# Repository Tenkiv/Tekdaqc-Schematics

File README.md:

# TekdaqcSchematics

pcb file for RevE and RevF are incomplete
- all digital grounds are currently unconnected
#TODO ground plane

RevE contains the files for the current Tekdaqc version

RevF is a modified version of the current Tekdaqc
- GIP15 is moved from PC14 to PH5
- GPI4 is moved from PH0 to PH3
- Digital Output connection has been modified to include a pull down resistor

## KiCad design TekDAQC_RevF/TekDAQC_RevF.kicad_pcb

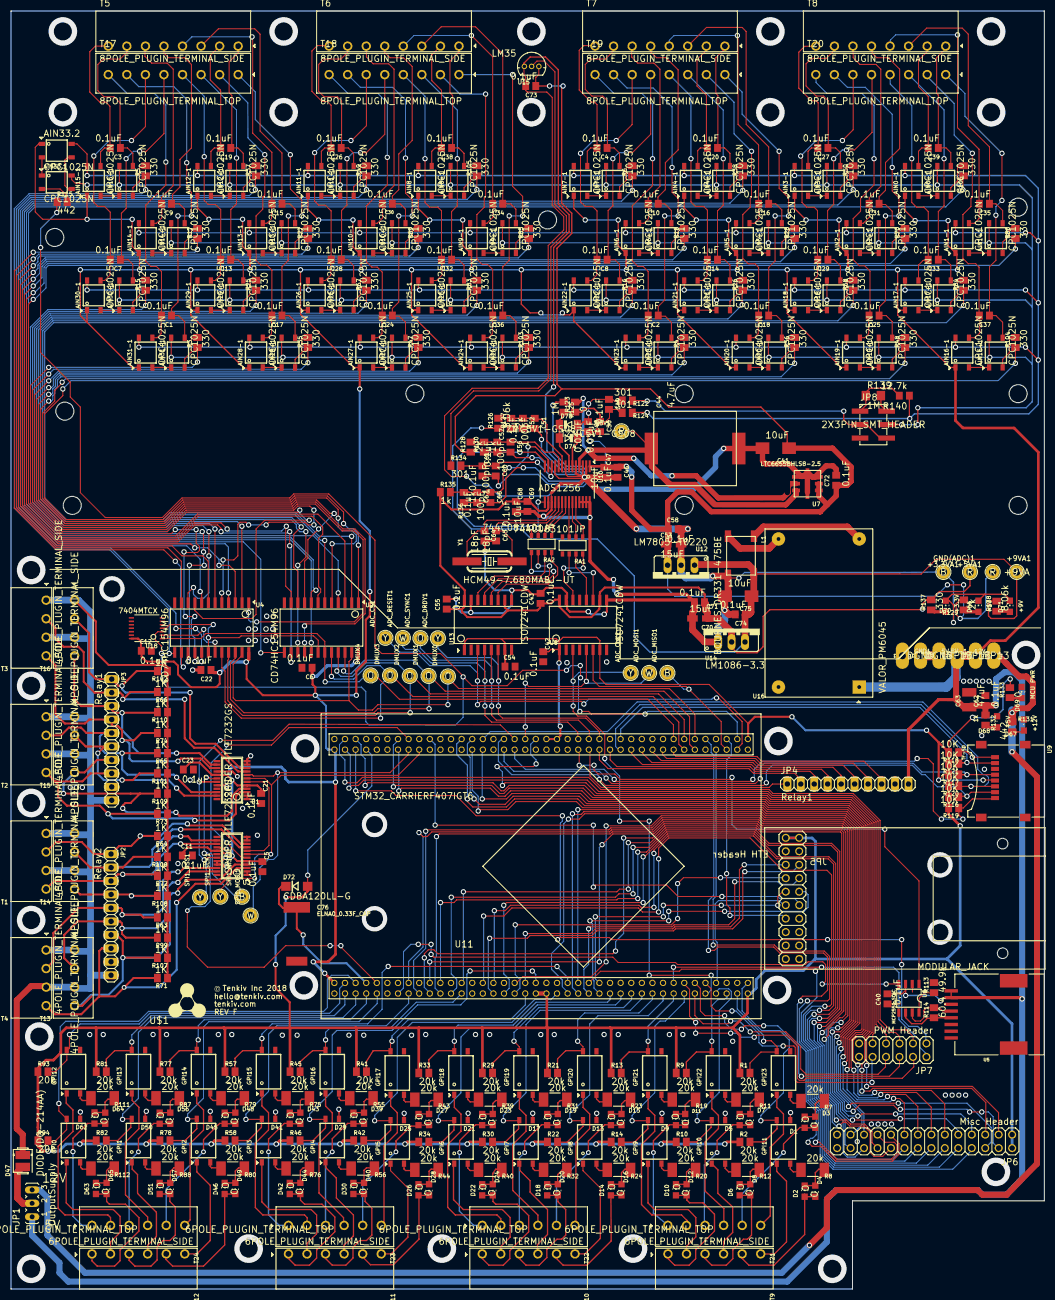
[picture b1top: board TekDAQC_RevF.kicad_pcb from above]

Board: 2 copper layers, 194.9 x 241.1 mm, 441 parts (0 on the bottom side), 430 nets.

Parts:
2.5V1: R; OTHER_KEYSTONE_5000
5V, 5V-1, 12V: LSP13
+3.3VA1, +5VA1: R; OTHER_KEYSTONE_5000
+9VA1: +9VA; OTHER_KEYSTONE_5000
@HOLE0, @HOLE1, @HOLE2, @HOLE3, @HOLE4, @HOLE6, @HOLE7, @HOLE8, @HOLE9, @HOLE10: (no value)
@HOLE5: HOLE_CIRCLE
@HOLE11, @HOLE12, @HOLE13, @HOLE14: HOLE_OVAL
ADC_CLK1: Y; OTHER_KEYSTONE_5000
ADC_CS1: Y; OTHER_KEYSTONE_5000
ADC_DRDY1: Y; OTHER_KEYSTONE_5000
ADC_MISO1: B; OTHER_KEYSTONE_5000
ADC_MOSI1: W; OTHER_KEYSTONE_5000
ADC_RESET1: W; OTHER_KEYSTONE_5000
ADC_SYNC1: O; OTHER_KEYSTONE_5000
AIN0+1, AIN0-1, AIN1+1, AIN1-1, AIN2+1, AIN2-1, AIN3+1, AIN3-1, AIN4+1, AIN4-1, AIN5+1, AIN5-1, AIN6+1, AIN6-1, AIN7+1, AIN7-1, AIN8+1, AIN8-1, AIN9+1, AIN9-1, AIN10+1, AIN10-1, AIN11+1, AIN11-1, AIN12+1, AIN12-1, AIN13+1, AIN13-1, AIN14+1, AIN14-1, AIN15+1, AIN15-1, AIN16+1, AIN16-1, AIN17+1, AIN17-1, AIN18+1, AIN18-1, AIN19+1, AIN19-1, AIN20+1, AIN20-1, AIN21+1, AIN21-1, AIN22+1, AIN22-1, AIN23+1, AIN23-1, AIN24+1, AIN24-1, AIN25+1, AIN25-1, AIN26+1, AIN26-1, AIN27+1, AIN27-1, AIN28+1, AIN28-1, AIN29+1, AIN29-1, AIN30+1, AIN30-1, AIN31+1, AIN31-1, AIN33.1, AIN33.2: CPC1025N; CPC1025N_SOP4
C1, C2, C3, C4, C5, C6, C7, C8, C9, C10, C11, C12, C13, C14, C15, C16, C17, C18, C19, C20, C21, C22, C23, C24, C25, C26, C27, C28, C29, C30, C31, C32, C33, C34, C35, C36, C37, C38, C39, C40, C42, C43, C46, C49, C52, C54, C55, C57, C58, C61, C62, C67, C68, C71, C72, C73, C74: 0.1uF; CAPACITOR_C0805
C41, C75: 10uF; CAPACITOR_CT6032
C44: 4.7uF; CAPACITOR_6054
C47, C69: 10uF; CAPACITOR_C0805
C48, C50: 0.01uF; CAPACITOR_C0805
C51, C56, C60, C66: 100pF; CAPACITOR_C0805
C53, C70: 15uF; CAPACITOR_CT3216
C63: 47uF; CAPACITOR_C1210
C64, C65: 18pF; CAPACITOR_C0805
C76: ELNA0_0.33F_CAP; COIN_CELL_CAP
D1, D2, D3, D4, D5, D6, D7, D8, D9, D10, D11, D12, D13, D14, D15, D16, D17, D18, D19, D20, D21, D22, D23, D24, D25, D26, D27, D28, D29, D30, D39, D40, D41, D42, D43, D44, D45, D46, D48, D49, D50, D51, D56, D57, D62, D63, D64, D65: O; LED_CHIPLED_0805
D47: DIODE(DO-214AA); DO−214AA
D66: +5V; LED_CHIPLED_0805
D67: +12V; CHIPLED_0805
D68: +5V; CHIPLED_0805
D69: MCU PWR; LED_CHIPLED_0805
D70: +3.3V; LED_CHIPLED_0805
D71: +9V; LED_CHIPLED_0805
D72: CDBA120LL-G; DIODE_DO214AC(SMA)
D73, D74: TZMC5V1-GS08; SOD80C
DMUX0, DMUX1, DMUX2, DMUX3, DMUX4: O; OTHER_KEYSTONE_5000
DRILEGEND: DRILEGEND
GND1: DGND; LSP13
GND(ADC)1: B; OTHER_KEYSTONE_5000
GPI0, GPI1, GPI2, GPI3, GPI4, GPI5, GPI6, GPI7, GPI8, GPI9, GPI10, GPI11, GPI12, GPI13, GPI14, GPI15, GPI16, GPI17, GPI18, GPI19, GPI20, GPI21, GPI22, GPI23: PS2505l_4-SMD
JP1: OutputSupply; JUMPER_JP2
JP2: Relay2; PINHEAD_1X10
JP3, JP4: Relay1; PINHEAD_1X10
JP5: ETH Header; TEKDAQC_ETH_2X10
JP6: Misc Header; PINHEAD_2X14
JP7: PWM Header; TEKDAQC_2X06
JP8: 2X3PIN_SMT_HEADER; HEADER_2X3SMT_HEADER
L1: BOURNES_DR331-475BE; DR331_CHOKE
R1, R2, R9, R10, R13, R14, R21, R22, R29, R30, R33, R34, R41, R42, R45, R46, R57, R58, R77, R78, R81, R82, R93, R94: 20k; RESISTOR_M0805
R3, R4, R5, R6, R15, R16, R17, R18, R25, R26, R27, R28, R35, R36, R37, R38, R47, R48, R49, R50, R67, R68, R69, R70, R83, R84, R85, R86, R103, R104, R105, R106, R137: 330; RESISTOR_M0805
R7, R8, R11, R12, R19, R20, R23, R24, R31, R32, R39, R40, R43, R44, R55, R56, R75, R76, R79, R80, R87, R88, R111, R112: 20k; RESISTOR_R2010
R63, R64, R65, R66, R71, R72, R73, R74, R99, R100, R101, R102, R107, R108, R109, R110: 1K; RESISTOR_M0805
R113: 49.9k; RESISTOR_M0805
R114: 60.4; RESISTOR_M0805
R115, R131: 442; RESISTOR_M0805
R116, R117, R118, R119, R120, R121: 10K; RESISTOR_M0805
R122, R124, R134: 301; RESISTOR_M0805
R123, R133: 0; RESISTOR_M0805
R125: 1M; RESISTOR_M0805
R126, R138: 8.06k; RESISTOR_M0805
R127, R128, R129: 2k; RESISTOR_M0805
R130, R132, R135, R136: 1k; RESISTOR_M0805
R139: 1M; RESISTOR_R1206
R140: 12.7k; RESISTOR_R0805
RA1, RA2: 744C083101JP; TEKDAQC_5131_744SERIES
SPI1_MISO1: B; OTHER_KEYSTONE_5000
SPI1_MOSI1: W; OTHER_KEYSTONE_5000
SPI1_NSS1, SPI1_SCK1: Y; OTHER_KEYSTONE_5000
T1, T2, T3, T4: 4POLE_PLUGIN_TERMINAL_SIDE; TEKDAQC_4POLE_3.5MM_TERMINAL_SIDE
T5, T6, T7, T8: 8POLE_PLUGIN_TERMINAL_SIDE; TEKDAQC_8POLE_3.5MM_TERMINAL_SIDE
T9, T10, T11, T12: 6POLE_PLUGIN_TERMINAL_SIDE; TEKDAQC_6POLE_3.5MM_TERMINAL_SIDE
T13, T14, T15, T16: 4POLE_PLUGIN_TERMINAL_SIDE; TEKDAQC_4POLE_3.5MM_TERMINAL_TOP
T17, T18, T19, T20: 8POLE_PLUGIN_TERMINAL_TOP; TEKDAQC_8POLE_3.5MM_TERMINAL_TOP
T21, T22, T23, T24: 6POLE_PLUGIN_TERMINAL_TOP; TEKDAQC_6POLE_3.5MM_TERMINAL_TOP
U1, U3: SPIDER-TLE7232GS; SPIDER_TLE7232GS_SSOP24
U2, U4: CD74HC154M96; CD74HC154M96_SOIC24
U5: MODULAR_JACK; MODULAR_JACK44144
U6: MCP2551_SOIC
U7: LTC6655BHLS8-2.5; LTC6655LS8_CLCC8
U8, U13: ISO7241CDW; ISO7241CDW_SOIC16
U9: TF-SD
U10: ADS1256; ADS1256_SSOP28
U11: STM32_CARRIERF407IGT6; STM32_CARRIER
U12: LM7805-T0220; V_REG_78XXS
U14: LM1086-3.3; V_REG_317TS
U15: LM35; LM35_TO_92
U16: VALOR_PM6045; DIL24_4PIN
U18: 7404MTCX; 7404MTCX_TSSOP14
U$1: TENKIV_INFO_BLOCK
Y1: HCM49-7.680MABJ-UT; CRYSTAL_HCM49

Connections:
2.5REF: 2.5V1.TP, C44.1, R123.2, U7.P$6, U7.P$7, U10.4
+5V: 5V.MP, 5V-1.MP, AIN0-1.1, AIN1-1.1, AIN2-1.1, AIN3-1.1, AIN4-1.1, AIN5-1.1, AIN6-1.1, AIN7-1.1, AIN8-1.1, AIN9-1.1, AIN10-1.1, AIN11-1.1, AIN12-1.1, AIN13-1.1, AIN14-1.1, AIN15-1.1, AIN16-1.1, AIN17-1.1, AIN18-1.1, AIN19-1.1, AIN20-1.1, AIN21-1.1, AIN22-1.1, AIN23-1.1, AIN24-1.1, AIN25-1.1, AIN26-1.1, AIN27-1.1, AIN28-1.1, AIN29-1.1, AIN30-1.1, AIN31-1.1, AIN33.2.1, C5.1, C6.1, C11.1, C12.1, C21.1, C22.1, C23.1, C40.2, C62.1, C63.1, JP1.1, JP4.10, R132.1, U1.5, U1.17, U2.24, U3.5, U3.17, U4.24, U5.1, U5.2, U6.3, U11.5V-I, U16.1, U18.14
+5V/1: +5VA1.TP, C41.+, C46.1, C47.1, C53.+, C58.1, C72.1, C73.1, R128.1, R129.2, U7.P$1, U7.P$2, U10.1, U12.OUT, U15.1
+9V: +9VA1.TP, C74.1, C75.+, L1.P$4, R126.1, R138.2, U12.IN, U14.3
+12V: 12V.MP, JP1.3, R131.1
/N$1: D68.A, R132.2
/N$4: D67.A, R131.2
/N$17: D69.A, R133.1
/N$105: R114.2, U5.4, U6.7
/N$106: R114.1, U5.5, U6.6
/N$107: R113.1, U6.8
/TekDAQC_RevF_AD.sch/DOUT: RA1.P$6, U8.11
/TekDAQC_RevF_AD.sch/N$2: AIN33.1.2, R115.2
/TekDAQC_RevF_AD.sch/N$3: RA2.P$3, U10.15
/TekDAQC_RevF_AD.sch/N$5: AIN33.1.1, AIN33.2.2
/TekDAQC_RevF_AD.sch/N$12: R134.1, U15.2
/TekDAQC_RevF_AD.sch/N$15: C48.1, C49.1, D73.A, D74.C, R122.2, U10.6
/TekDAQC_RevF_AD.sch/N$16: C49.2, C50.1, D73.C, D74.A, R123.1, R124.2, R125.2, U10.7
/TekDAQC_RevF_AD.sch/N$20: C65.1, U10.19, Y1.P$1
/TekDAQC_RevF_AD.sch/N$21: C64.1, U10.18, Y1.P$2
/TekDAQC_RevF_AD.sch/N$23: RA1.P$2, U10.23
/TekDAQC_RevF_AD.sch/N$24: RA1.P$1, U10.24
/TekDAQC_RevF_AD.sch/N$28: D70.A, R137.1
/TekDAQC_RevF_AD.sch/N$29: RA1.P$8, U8.14
/TekDAQC_RevF_AD.sch/N$30: RA1.P$7, U8.12
/TekDAQC_RevF_AD.sch/N$108: RA2.P$2, U10.20
/TekDAQC_RevF_AD.sch/N$110: AIN33.1.3, AIN33.2.3
/TekDAQC_RevF_AD.sch/N$114: L1.P$1, U16.12
/TekDAQC_RevF_AD.sch/N$116: JP8.P$2, JP8.P$4, R122.1
/TekDAQC_RevF_AD.sch/N$117: L1.P$2, U16.13
/TekDAQC_RevF_AD.sch/N$124: JP8.P$6, R139.2
/TekDAQC_RevF_AD.sch/N$125: JP8.P$1, R139.1, R140.2
/TekDAQC_RevF_AD.sch/N$149: RA2.P$1, U10.21
/TekDAQC_RevF_AD.sch/N$152: RA2.P$4, U10.14
/TekDAQC_RevF_AD.sch/N$153: RA2.P$8, U13.11
/TekDAQC_RevF_AD.sch/N$154: RA2.P$5, U13.12
/TekDAQC_RevF_AD.sch/N$155: RA2.P$6, U13.13
/TekDAQC_RevF_AD.sch/N$156: RA2.P$7, U13.14
/TekDAQC_RevF_AD.sch/N$160: C51.1, C52.1, R126.2, R127.2, U10.9
/TekDAQC_RevF_AD.sch/N$161: RA1.P$3, U10.22
/TekDAQC_RevF_AD.sch/N$162: D71.A, R138.1
/TekDAQC_RevF_AD.sch/N$163: D66.A, R129.1
/TekDAQC_RevF_AD.sch/N$164: C66.1, C67.1, R135.2, R136.2, U10.13
/TekDAQC_RevF_AD.sch/N$165: C60.1, C61.1, R134.2, U10.12
/TekDAQC_RevF_AD.sch/N$166: C56.1, C57.1, R128.2, R130.2, U10.10
/TekDAQC_RevF_AI/N$18: AIN0+1.2, R106.2
/TekDAQC_RevF_AI/N$19: AIN1+1.2, R86.2
/TekDAQC_RevF_AI/N$22: AIN0+1.1, AIN0-1.2
/TekDAQC_RevF_AI/N$31: AIN24+1.1, AIN24-1.2
/TekDAQC_RevF_AI/N$33: AIN24+1.2, R103.2
/TekDAQC_RevF_AI/N$34: AIN1+1.1, AIN1-1.2
/TekDAQC_RevF_AI/N$35: AIN2+1.1, AIN2-1.2
/TekDAQC_RevF_AI/N$36: AIN2+1.2, R70.2
/TekDAQC_RevF_AI/N$37: AIN3+1.2, R50.2
/TekDAQC_RevF_AI/N$38: AIN3+1.1, AIN3-1.2
/TekDAQC_RevF_AI/N$39: AIN4+1.1, AIN4-1.2
/TekDAQC_RevF_AI/N$40: AIN4+1.2, R38.2
/TekDAQC_RevF_AI/N$41: AIN5+1.2, R28.2
/TekDAQC_RevF_AI/N$42: AIN6+1.2, R18.2
/TekDAQC_RevF_AI/N$43: AIN5+1.1, AIN5-1.2
/TekDAQC_RevF_AI/N$44: AIN6+1.1, AIN6-1.2
/TekDAQC_RevF_AI/N$45: AIN7+1.1, AIN7-1.2
/TekDAQC_RevF_AI/N$46: AIN7+1.2, R6.2
/TekDAQC_RevF_AI/N$47: AIN8+1.2, R105.2
/TekDAQC_RevF_AI/N$48: AIN8+1.1, AIN8-1.2
/TekDAQC_RevF_AI/N$49: AIN9+1.1, AIN9-1.2
/TekDAQC_RevF_AI/N$50: AIN9+1.2, R85.2
/TekDAQC_RevF_AI/N$51: AIN10+1.2, R69.2
/TekDAQC_RevF_AI/N$52: AIN10+1.1, AIN10-1.2
/TekDAQC_RevF_AI/N$53: AIN11+1.1, AIN11-1.2
/TekDAQC_RevF_AI/N$54: AIN11+1.2, R49.2
/TekDAQC_RevF_AI/N$55: AIN12+1.1, AIN12-1.2
/TekDAQC_RevF_AI/N$56: AIN12+1.2, R37.2
/TekDAQC_RevF_AI/N$57: AIN13+1.1, AIN13-1.2
/TekDAQC_RevF_AI/N$58: AIN13+1.2, R27.2
/TekDAQC_RevF_AI/N$59: AIN14+1.1, AIN14-1.2
/TekDAQC_RevF_AI/N$60: AIN14+1.2, R17.2
/TekDAQC_RevF_AI/N$61: AIN15+1.1, AIN15-1.2
/TekDAQC_RevF_AI/N$62: AIN15+1.2, R5.2
/TekDAQC_RevF_AI/N$63: AIN25+1.2, R83.2
/TekDAQC_RevF_AI/N$64: AIN25+1.1, AIN25-1.2
/TekDAQC_RevF_AI/N$65: AIN26+1.1, AIN26-1.2
/TekDAQC_RevF_AI/N$66: AIN26+1.2, R67.2
/TekDAQC_RevF_AI/N$67: AIN27+1.1, AIN27-1.2
/TekDAQC_RevF_AI/N$68: AIN27+1.2, R47.2
/TekDAQC_RevF_AI/N$69: AIN28+1.1, AIN28-1.2
/TekDAQC_RevF_AI/N$70: AIN28+1.2, R35.2
/TekDAQC_RevF_AI/N$71: AIN29+1.1, AIN29-1.2
/TekDAQC_RevF_AI/N$72: AIN29+1.2, R25.2
/TekDAQC_RevF_AI/N$73: AIN30+1.1, AIN30-1.2
/TekDAQC_RevF_AI/N$74: AIN30+1.2, R15.2
/TekDAQC_RevF_AI/N$75: AIN31+1.1, AIN31-1.2
/TekDAQC_RevF_AI/N$76: AIN31+1.2, R3.2
/TekDAQC_RevF_AI/N$78: AIN16+1.2, R104.2
/TekDAQC_RevF_AI/N$79: AIN17+1.2, R84.2
/TekDAQC_RevF_AI/N$80: AIN18+1.2, R68.2
/TekDAQC_RevF_AI/N$81: AIN19+1.2, R48.2
/TekDAQC_RevF_AI/N$83: AIN20+1.2, R36.2
/TekDAQC_RevF_AI/N$84: AIN21+1.2, R26.2
/TekDAQC_RevF_AI/N$85: AIN22+1.2, R16.2
/TekDAQC_RevF_AI/N$86: AIN23+1.2, R4.2
/TekDAQC_RevF_AI/N$87: AIN16+1.1, AIN16-1.2
/TekDAQC_RevF_AI/N$88: AIN17+1.1, AIN17-1.2
/TekDAQC_RevF_AI/N$89: AIN18+1.1, AIN18-1.2
/TekDAQC_RevF_AI/N$90: AIN19+1.1, AIN19-1.2
/TekDAQC_RevF_AI/N$91: AIN20+1.1, AIN20-1.2
/TekDAQC_RevF_AI/N$92: AIN21+1.1, AIN21-1.2
/TekDAQC_RevF_AI/N$93: AIN22+1.1, AIN22-1.2
/TekDAQC_RevF_AI/N$94: AIN23+1.1, AIN23-1.2
/TekDAQC_RevF_DI.sch/N$186: GPI1.2, R88.2
/TekDAQC_RevF_DI.sch/N$187: GPI2.2, R80.2
/TekDAQC_RevF_DI.sch/N$188: GPI3.2, R76.2
/TekDAQC_RevF_DI.sch/N$189: GPI4.2, R56.2
/TekDAQC_RevF_DI.sch/N$190: GPI5.2, R44.2
/TekDAQC_RevF_DI.sch/N$191: GPI6.2, R40.2
/TekDAQC_RevF_DI.sch/N$192: GPI7.2, R32.2
/TekDAQC_RevF_DI.sch/N$193: GPI8.2, R24.2
/TekDAQC_RevF_DI.sch/N$194: GPI9.2, R20.2
/TekDAQC_RevF_DI.sch/N$195: GPI10.2, R12.2
/TekDAQC_RevF_DI.sch/N$196: GPI11.2, R8.2
/TekDAQC_RevF_DI.sch/N$197: GPI12.2, R111.2
/TekDAQC_RevF_DI.sch/N$198: GPI13.2, R87.2
/TekDAQC_RevF_DI.sch/N$199: GPI14.2, R79.2
/TekDAQC_RevF_DI.sch/N$200: GPI15.2, R75.2
/TekDAQC_RevF_DI.sch/N$201: GPI16.2, R55.2
/TekDAQC_RevF_DI.sch/N$202: GPI17.2, R43.2
/TekDAQC_RevF_DI.sch/N$203: GPI18.2, R39.2
/TekDAQC_RevF_DI.sch/N$204: GPI19.2, R31.2
/TekDAQC_RevF_DI.sch/N$205: GPI20.2, R23.2
/TekDAQC_RevF_DI.sch/N$206: GPI21.2, R19.2
/TekDAQC_RevF_DI.sch/N$207: GPI22.2, R11.2
/TekDAQC_RevF_DI.sch/N$208: GPI23.2, R7.2
/TekDAQC_RevF_DI.sch/N$209: GPI0.2, R112.2
/TekDAQC_RevF_DI.sch/N$211: D63.C, D65.A, R112.1
/TekDAQC_RevF_DI.sch/N$212: D51.C, D57.A, R88.1
/TekDAQC_RevF_DI.sch/N$213: D46.C, D49.A, R80.1
/TekDAQC_RevF_DI.sch/N$214: D42.C, D44.A, R76.1
/TekDAQC_RevF_DI.sch/N$215: D30.C, D40.A, R56.1
/TekDAQC_RevF_DI.sch/N$216: D26.C, D28.A, R44.1
/TekDAQC_RevF_DI.sch/N$217: D22.C, D24.A, R40.1
/TekDAQC_RevF_DI.sch/N$218: D18.C, D20.A, R32.1
/TekDAQC_RevF_DI.sch/N$219: D14.C, D16.A, R24.1
/TekDAQC_RevF_DI.sch/N$220: D10.C, D12.A, R20.1
/TekDAQC_RevF_DI.sch/N$221: D6.C, D8.A, R12.1
/TekDAQC_RevF_DI.sch/N$222: D2.C, D4.A, R8.1
/TekDAQC_RevF_DI.sch/N$223: D62.C, D64.A, R111.1
/TekDAQC_RevF_DI.sch/N$224: D50.C, D56.A, R87.1
/TekDAQC_RevF_DI.sch/N$225: D45.C, D48.A, R79.1
/TekDAQC_RevF_DI.sch/N$226: D41.C, D43.A, R75.1
/TekDAQC_RevF_DI.sch/N$227: D29.C, D39.A, R55.1
/TekDAQC_RevF_DI.sch/N$228: D25.C, D27.A, R43.1
/TekDAQC_RevF_DI.sch/N$229: D21.C, D23.A, R39.1
/TekDAQC_RevF_DI.sch/N$230: D17.C, D19.A, R31.1
/TekDAQC_RevF_DI.sch/N$231: D13.C, D15.A, R23.1
/TekDAQC_RevF_DI.sch/N$232: D9.C, D11.A, R19.1
/TekDAQC_RevF_DI.sch/N$233: D5.C, D7.A, R11.1
/TekDAQC_RevF_DI.sch/N$234: D1.C, D3.A, R7.1
/TekDAQC_RevF_DO.sch//DMUX4: U4.19, U18.2
/TekDAQC_RevF_DO.sch/N$77: D47.2, JP2.10, JP3.10, R63.1, R64.1, R65.1, R66.1, R71.1, R72.1, R73.1, R74.1, R99.1, R100.1, R101.1, R102.1, R107.1, R108.1, R109.1, R110.1, T1.1, T1.3, T2.1, T2.3, T3.1, T3.3, T4.1, T4.3, T13.1, T13.3, T14.1, T14.3, T15.1, T15.3, T16.1, T16.3
/TekDAQC_RevF_DO.sch/N$82: U1.6, U3.8
/TekDAQC_RevF_DO.sch/N$118: D47.1, JP1.2
/TekDAQC_RevF_DO.sch/OCAL_: U2.18, U4.18, U18.4
/VBAT: C76.P$1, D72.C, U11.VBAT
ADC1_IN0: JP6.4, U11.PA0
ADC1_IN3: JP6.6, U11.PA3
ADC1_IN6: JP6.8, U11.PA6
ADC2_IN10: JP6.10, U11.PC0
ADC2_IN12: JP6.12, U11.PC2
ADC2_IN13: JP6.14, U11.PC3
ADC3_IN4: JP6.16, U11.PF6
ADC3_IN5: JP6.18, U11.PF7
ADC3_IN8: JP6.20, U11.PF10
ADC3_IN9: JP6.22, U11.PF3
ADC3_IN14: JP6.24, U11.PF4
ADC3_IN15: JP6.26, U11.PF5
AIN0: AIN0+1.4, AIN1+1.4, AIN2+1.4, AIN3+1.4, AIN4+1.4, AIN5+1.4, AIN6+1.4, AIN7+1.4, AIN8+1.4, AIN9+1.4, AIN10+1.4, AIN11+1.4, AIN12+1.4, AIN13+1.4, AIN14+1.4, AIN15+1.4, AIN16+1.4, AIN17+1.4, AIN18+1.4, AIN19+1.4, AIN20+1.4, AIN21+1.4, AIN22+1.4, AIN23+1.4, AIN24+1.4, AIN25+1.4, AIN26+1.4, AIN27+1.4, AIN28+1.4, AIN29+1.4, AIN30+1.4, AIN31+1.4, AIN33.1.4, JP8.P$5
AIN1: AIN0-1.4, AIN1-1.4, AIN2-1.4, AIN3-1.4, AIN4-1.4, AIN5-1.4, AIN6-1.4, AIN7-1.4, AIN8-1.4, AIN9-1.4, AIN10-1.4, AIN11-1.4, AIN12-1.4, AIN13-1.4, AIN14-1.4, AIN15-1.4, AIN16-1.4, AIN17-1.4, AIN18-1.4, AIN19-1.4, AIN20-1.4, AIN21-1.4, AIN22-1.4, AIN23-1.4, AIN24-1.4, AIN25-1.4, AIN26-1.4, AIN27-1.4, AIN28-1.4, AIN29-1.4, AIN30-1.4, AIN31-1.4, AIN33.2.4, R124.1, R140.1
CAN1_RX: U6.4, U11.PI9
CAN1_TX: U6.1, U11.PH13
DAC_OUT1: JP6.23, U11.PA4
DAC_OUT2: JP6.25, U11.PA5
DGND: C5.2, C6.2, C11.2, C12.2, C21.2, C22.2, C23.2, C40.1, C42.2, C54.2, C62.2, C63.2, C76.P$2, D67.C, D68.C, D69.C, GND1.MP, GPI0.3, GPI1.3, GPI2.3, GPI3.3, GPI4.3, GPI5.3, GPI6.3, GPI7.3, GPI8.3, GPI9.3, GPI10.3, GPI11.3, GPI12.3, GPI13.3, GPI14.3, GPI15.3, GPI16.3, GPI17.3, GPI18.3, GPI19.3, GPI20.3, GPI21.3, GPI22.3, GPI23.3, JP2.9, JP3.9, JP4.9, JP5.3, JP5.4, JP6.27, JP6.28, JP7.11, JP7.12, R113.2, U1.1, U1.2, U1.11, U1.12, U1.16, U1.20, U1.21, U2.12, U3.1, U3.2, U3.11, U3.12, U3.16, U3.20, U3.21, U4.12, U5.3, U5.6, U5.7, U5.8, U5.G1, U5.G2, U6.2, U8.2, U8.8, U9.G1, U9.G2, U9.G3, U9.G4, U9.PIN6, U11.GND-, U13.2, U13.8, U16.24, U18.5, U18.7, U18.9, U18.11, U18.13
DMUX0: DMUX0.TP, U2.23, U4.23, U11.PD11
DMUX1: DMUX1.TP, U2.22, U4.22, U11.PD12
DMUX2: DMUX2.TP, U2.21, U4.21, U11.PD13
DMUX3: DMUX3.TP, U2.20, U4.20, U11.PD14
DMUX4: DMUX4.TP, U2.19, U11.PD15, U18.1
ETH_RMII_CRS_DV: JP5.8, U11.PA7
ETH_RMII_MDC: JP5.6, U11.PC1
ETH_RMII_MDIO: JP5.5, U11.PA2
ETH_RMII_REF_CLK: JP5.7, U11.PA1
ETH_RMII_RXD0: JP5.9, U11.PC4
ETH_RMII_RXD1: JP5.10, U11.PC5
ETH_RMII_TXD0: JP5.12, U11.PG13
ETH_RMII_TXD1: JP5.13, U11.PB13
ETH_RMII_TX_EN: JP5.11, U11.PB11
GND: C41.-, C43.2, C44.2, C46.2, C47.2, C48.2, C50.2, C51.2, C52.2, C53.-, C55.2, C56.2, C57.2, C58.2, C60.2, C61.2, C64.2, C65.2, C66.2, C67.2, C68.2, C69.2, C70.-, C71.2, C72.2, C73.2, C74.2, C75.-, D66.C, D70.C, D71.C, GND(ADC)1.TP, L1.P$3, R125.1, R127.1, R130.1, R136.1, U7.P$3, U7.P$4, U7.P$5, U7.P$8, U8.9, U8.15, U10.2, U10.3, U10.5, U10.8, U10.11, U10.17, U10.25, U10.26, U10.27, U10.28, U12.GND, U13.9, U13.15, U14.1, U15.3
GPI0: GPI0.4, R94.2, U11.PE5
GPI0+: GPI0.1, T12.2
GPI0-: D63.A, D65.C, T12.1
GPI1: GPI1.4, R82.2, U11.PE4
GPI1+: GPI1.1, T12.4
GPI1-: D51.A, D57.C, T12.3
GPI2: GPI2.4, R78.2, U11.PI8
GPI2+: GPI2.1, T12.6
GPI2-: D46.A, D49.C, T12.5
GPI3: GPI3.4, R58.2, U11.PI11
GPI3+: GPI3.1, T11.2
GPI3-: D42.A, D44.C, T11.1
GPI4: GPI4.4, R46.2, U11.PH3
GPI4+: GPI4.1, T11.4
GPI4-: D30.A, D40.C, T11.3
GPI5: GPI5.4, R42.2, U11.PH4
GPI5+: GPI5.1, T11.6
GPI5-: D26.A, D28.C, T11.5
GPI6: GPI6.4, R34.2, U11.PF11
GPI6+: GPI6.1, T10.2
GPI6-: D22.A, D24.C, T10.1
GPI7: GPI7.4, R30.2, U11.PF15
GPI7+: GPI7.1, T10.4
GPI7-: D18.A, D20.C, T10.3
GPI8: GPI8.4, R22.2, U11.PE8
GPI8+: GPI8.1, T10.6
GPI8-: D14.A, D16.C, T10.5
GPI9: GPI9.4, R14.2, U11.PE12
GPI9+: GPI9.1, T9.2
GPI9-: D10.A, D12.C, T9.1
GPI10: GPI10.4, R10.2, U11.PH6
GPI10+: GPI10.1, T9.4
GPI10-: D6.A, D8.C, T9.3
GPI11: GPI11.4, R2.2, U11.PH11
GPI11+: GPI11.1, T9.6
GPI11-: D2.A, D4.C, T9.5
GPI12: GPI12.4, R93.2, U11.PE3
GPI12+: GPI12.1, T24.2
GPI12-: D62.A, D64.C, T24.1
GPI13: GPI13.4, R81.2, U11.PE2
GPI13+: GPI13.1, T24.4
GPI13-: D50.A, D56.C, T24.3
GPI14: GPI14.4, R77.2, U11.PE6
GPI14+: GPI14.1, T24.6
GPI14-: D45.A, D48.C, T24.5
GPI15: GPI15.4, R57.2, U11.PH5
GPI15+: GPI15.1, T23.2
GPI15-: D41.A, D43.C, T23.1
GPI16: GPI16.4, R45.2, U11.PF9
GPI16+: GPI16.1, T23.4
GPI16-: D29.A, D39.C, T23.3
GPI17: GPI17.4, R41.2, U11.PH2
GPI17+: GPI17.1, T23.6
GPI17-: D25.A, D27.C, T23.5
GPI18: GPI18.4, R33.2, U11.PB1
GPI18+: GPI18.1, T22.2
GPI18-: D21.A, D23.C, T22.1
GPI19: GPI19.4, R29.2, U11.PF13
GPI19+: GPI19.1, T22.4
GPI19-: D17.A, D19.C, T22.3
GPI20: GPI20.4, R21.2, U11.PG1
GPI20+: GPI20.1, T22.6
GPI20-: D13.A, D15.C, T22.5
GPI21: GPI21.4, R13.2, U11.PE10
GPI21+: GPI21.1, T21.2
GPI21-: D9.A, D11.C, T21.1
GPI22: GPI22.4, R9.2, U11.PH8
GPI22+: GPI22.1, T21.4
GPI22-: D5.A, D7.C, T21.3
GPI23: GPI23.4, R1.2, U11.PH10
GPI23+: GPI23.1, T21.6
GPI23-: D1.A, D3.C, T21.5
I2C1_SCL: JP6.3, U11.PB6
I2C1_SDA: JP6.5, U11.PB7
I2C2_SCL: JP6.7, U11.PF1
I2C2_SDA: JP6.9, U11.PF0
OCAL: R115.1, U11.PH12, U18.3
REL1_IN1: JP4.8, U11.PG2
REL1_IN2: JP4.7, U11.PG4
REL1_IN3: JP4.6, U11.PG6
REL1_IN4: JP4.5, U11.PG8
REL1_IN5: JP4.4, U11.PC7
REL1_IN6: JP4.3, U11.PA9
REL1_IN7: JP4.2, U11.PA11
REL1_IN8: JP4.1, U11.PA13
SDIO_CLK: R117.1, U9.PIN5, U11.PC12
SDIO_CMD: R120.1, U9.PIN3, U11.PD2
SDIO_D0: R121.1, U9.PIN7, U11.PC8
SDIO_D1: R118.1, U9.PIN8, U11.PC9
SDIO_D2: R119.1, U9.PIN1, U11.PC10
SDIO_D3: R116.1, U9.PIN2, U11.PC11
SENS1: R106.1, U2.4
SENS2: R86.1, U2.3
SENS3: R70.1, U2.7
SENS4: R50.1, U2.8
SENS5: R38.1, U2.17
SENS6: R28.1, U2.11
SENS7: R18.1, U2.14
SENS8: R6.1, U2.13
SENS9: R105.1, U4.4
SENS10: R85.1, U4.3
SENS11: R69.1, U4.7
SENS12: R49.1, U4.8
SENS13: R37.1, U4.17
SENS14: R27.1, U4.11
SENS15: R17.1, U4.14
SENS16: R5.1, U4.13
SENS17: R104.1, U2.1
SENS18: R84.1, U2.2
SENS19: R68.1, U2.6
SENS20: R48.1, U2.5
SENS21: R36.1, U2.9
SENS22: R26.1, U2.10
SENS23: R16.1, U2.15
SENS24: R4.1, U2.16
SENS25: R103.1, U4.1
SENS26: R83.1, U4.2
SENS27: R67.1, U4.6
SENS28: R47.1, U4.5
SENS29: R35.1, U4.9
SENS30: R25.1, U4.10
SENS31: R15.1, U4.15
SENS32: R3.1, U4.16
SPI1_MISO: SPI1_MISO1.TP, U3.6, U11.PB4
SPI1_MOSI: SPI1_MOSI1.TP, U1.8, U11.PB5
SPI1_NSS: SPI1_NSS1.TP, U1.19, U3.19, U11.PA15
SPI1_SCK: SPI1_SCK1.TP, U1.7, U3.7, U11.PB3
SPI2_DRDY: ADC_DRDY1.TP, U11.PA10, U13.6
SPI2_MISO: ADC_MISO1.TP, U8.6, U11.PB14
SPI2_MOSI: ADC_MOSI1.TP, U8.5, U11.PI3
SPI2_NSS: ADC_CS1.TP, U11.PB12, U13.3
SPI2_RST: ADC_RESET1.TP, U11.PH14, U13.4
SPI2_SCK: ADC_CLK1.TP, U8.3, U11.PB10
SPI2_SYNC: ADC_SYNC1.TP, U11.PA12, U13.5
SPIDER_RST: U1.18, U3.18, U11.PC13
T1.1: AIN0+1.3, C39.1, T8.1
T1.2: AIN0-1.3, C39.2, T8.2
T1.3: AIN1+1.3, C35.1, T8.3
T1.4: AIN1-1.3, C35.2, T8.4
T1.5: AIN2+1.3, C31.1, T8.5
T1.6: AIN2-1.3, C31.2, T8.6
T1.7: AIN3+1.3, C27.1, T8.7
T1.8: AIN3-1.3, C27.2, T8.8
T2.1: AIN4+1.3, C20.1, T7.1
T2.2: AIN4-1.3, C20.2, T7.2
T2.3: AIN5+1.3, C16.1, T7.3
T2.4: AIN5-1.3, C16.2, T7.4
T2.5: AIN6+1.3, C10.1, T7.5
T2.6: AIN6-1.3, C10.2, T7.6
T2.7: AIN7+1.3, C4.1, T7.7
T2.8: AIN7-1.3, C4.2, T7.8
T3.1: AIN8+1.3, C38.1, T6.1
T3.2: AIN8-1.3, C38.2, T6.2
T3.3: AIN9+1.3, C34.1, T6.3
T3.4: AIN9-1.3, C34.2, T6.4
T3.5: AIN10+1.3, C30.1, T6.5
T3.6: AIN10-1.3, C30.2, T6.6
T3.7: AIN11+1.3, C26.1, T6.7
T3.8: AIN11-1.3, C26.2, T6.8
T4.1: AIN12+1.3, C19.1, T5.1
T4.2: AIN12-1.3, C19.2, T5.2
T4.3: AIN13+1.3, C15.1, T5.3
T4.4: AIN13-1.3, C15.2, T5.4
T4.5: AIN14+1.3, C9.1, T5.5
T4.6: AIN14-1.3, C9.2, T5.6
T4.7: AIN15+1.3, C3.1, T5.7
T4.8: AIN15-1.3, C3.2, T5.8
T5.1: AIN16+1.3, C37.1, T20.1
T5.2: AIN16-1.3, C37.2, T20.2
T5.3: AIN17+1.3, C33.1, T20.3
T5.4: AIN17-1.3, C33.2, T20.4
T5.5: AIN18+1.3, C29.1, T20.5
T5.6: AIN18-1.3, C29.2, T20.6
T5.7: AIN19+1.3, C25.1, T20.7
T5.8: AIN19-1.3, C25.2, T20.8
T6.1: AIN20+1.3, C18.1, T19.1
T6.2: AIN20-1.3, C18.2, T19.2
T6.3: AIN21+1.3, C14.1, T19.3
T6.4: AIN21-1.3, C14.2, T19.4
T6.5: AIN22+1.3, C8.1, T19.5
T6.6: AIN22-1.3, C8.2, T19.6
T6.7: AIN23+1.3, C2.1, T19.7
T6.8: AIN23-1.3, C2.2, T19.8
T7.1: AIN24+1.3, C36.1, T18.1
T7.2: AIN24-1.3, C36.2, T18.2
T7.3: AIN25+1.3, C32.1, T18.3
T7.4: AIN25-1.3, C32.2, T18.4
T7.5: AIN26+1.3, C28.1, T18.5
T7.6: AIN26-1.3, C28.2, T18.6
T7.7: AIN27+1.3, C24.1, T18.7
T7.8: AIN27-1.3, C24.2, T18.8
T8.1: AIN28+1.3, C17.1, T17.1
T8.2: AIN28-1.3, C17.2, T17.2
T8.3: AIN29+1.3, C13.1, T17.3
T8.4: AIN29-1.3, C13.2, T17.4
T8.5: AIN30+1.3, C7.1, T17.5
T8.6: AIN30-1.3, C7.2, T17.6
T8.7: AIN31+1.3, C1.1, T17.7
T8.8: AIN31-1.3, C1.2, T17.8
T9.2: JP3.2, R66.2, T3.2, U1.9
T9.4: JP3.4, R74.2, T3.4, U1.15
T10.2: JP3.5, R65.2, T2.2, U1.22
T10.4: JP3.8, R73.2, T2.4, U1.3
T11.2: JP2.1, R64.2, T1.2, U3.10
T11.4: JP2.3, R72.2, T1.4, U3.14
T12.2: JP2.5, R63.2, T4.2, U3.22
T12.4: JP2.8, R71.2, T4.4, U3.3
T13.2: JP3.1, R102.2, T16.2, U1.10
T13.4: JP3.3, R110.2, T16.4, U1.14
T14.2: JP3.6, R101.2, T15.2, U1.23
T14.4: JP3.7, R109.2, T15.4, U1.4
T15.2: JP2.2, R100.2, T14.2, U3.9
T15.4: JP2.4, R108.2, T14.4, U3.15
T16.2: JP2.6, R99.2, T13.2, U3.23
T16.4: JP2.7, R107.2, T13.4, U3.4
TIM1_BKIN: JP7.10, U11.PE15
TIM1_CH1: JP7.2, U11.PE9
TIM1_CH2: JP7.4, U11.PE11
TIM1_CH3: JP7.6, U11.PE13
TIM1_CH4: JP7.8, U11.PE14
TIM8_BKIN: JP7.9, U11.PI4
TIM8_CH1: JP7.1, U11.PI5
TIM8_CH2: JP7.3, U11.PI6
TIM8_CH3: JP7.5, U11.PI7
TIM8_CH4: JP7.7, U11.PI2
USART2_CTS: JP6.11, U11.PD3
USART2_RTS: JP6.13, U11.PD4
USART2_RX: JP6.15, U11.PD6
USART2_TX: JP6.17, U11.PD5
USART3_RX: JP6.19, U11.PD9
USART3_TX: JP6.21, U11.PD8
VCC: C42.1, C54.1, D72.A, JP5.1, JP5.2, JP6.1, JP6.2, R1.1, R2.1, R9.1, R10.1, R13.1, R14.1, R21.1, R22.1, R29.1, R30.1, R33.1, R34.1, R41.1, R42.1, R45.1, R46.1, R57.1, R58.1, R77.1, R78.1, R81.1, R82.1, R93.1, R94.1, R116.2, R117.2, R118.2, R119.2, R120.2, R121.2, R133.2, U8.1, U8.7, U9.PIN4, U11.3.3V, U11.PDR, U13.1, U13.7
VDD: +3.3VA1.TP, C43.1, C55.1, C68.1, C69.1, C70.+, C71.1, R135.1, R137.2, U8.10, U8.16, U10.16, U13.10, U13.16, U14.2

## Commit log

2018-03-20 Init Repo
2018-03-22 Create emptyFile
2018-03-22 schematic/pcb/library files
    schematic files - '*.sch'
    pcb file - '*.brd'
    library - '*.lib'
    net - '*.net'
2018-03-22 Footprints used on pcb board
2018-03-22 renamed: TekDaqc_RevE/TekDAQC_RevE.pretty/TekDAQC_RevE.pretty/7404MTCX_TSSOP14.kicad_mod -> TekDaqc_RevE/TekDAQC_RevE.pretty/7404MTCX_TSSOP14.kicad_mod renamed: TekDaqc_RevE/TekDAQC_RevE.pretty/TekDA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
2018-03-22 general file explanation
2018-05-02 **Notes**
2018-05-06 current tekdaqc unmodified
2018-05-06 new file: TekDAQC_RevF/TekDAQC_RevF.kicad_pcb new file: TekDAQC_RevF/TekDAQC_RevF.lib new file: TekDAQC_RevF/TekDAQC_RevF.net new file: TekDAQC_RevF/TekDAQC_RevF.pretty/7404MTCX_TSSOP14.kicad_mod new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
2018-05-06 added a readme for RevF
2018-08-13 Add LICENSE
